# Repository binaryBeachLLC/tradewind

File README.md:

# Tradewind TW-1 · solar LoRaWAN field sensor

Tradewind is a sealed, solar-powered sensor for farms and remote sites. It measures air temperature and humidity,
soil moisture and rainfall, and reports over LoRaWAN every 5 minutes (every minute in rapid mode). It is a complete
reference design by [Binary Beach](https://binarybeach.tech): requirements, simulation, schematic, a 4-layer board,
enclosure, firmware, bring-up, characterization and a 30-day field pilot.

**The full story is in the documents. This README is a map of the repository.**

| | |
|---|---|
| 📘 [Engineering design & test report](docs/Tradewind_TW-1_Engineering_Report_revB.pdf) (46 pages) | requirements, simulation, schematic, electrical and layout considerations, EMI/EMC, enclosure, bring-up, test and field data |
| 📗 [Product datasheet](docs/Tradewind_TW-1_Datasheet_revB.pdf) (14 pages) | specifications, typical characteristics, connector functions, drawings, ordering |
| 🌐 [Interactive page](https://binarybeach.tech/hardware/tradewind/) | the product and the board in 3D, the schematic and the PCB layers in the browser |

## Results at a glance (rev B)

| | Measured | Requirement |
|---|---|---|
| Sleep current, whole device | 7.2 µA mean, 8.1 µA max (10 boards) | ≤ 10 µA |
| Average current, 5-min SF9 | 75.9 µA | ≤ 100 µA |
| Days with no sun at all, 1-min mode | ≈ 250 | ≥ 60 |
| Radio range, line of sight | decoded at 13.2 km (SF10) | ≥ 5 km |
| Air temperature error, −10 to +60 °C | 0.20 °C worst | ±0.3 °C |
| Hottest cell, 30 days in Hawaiʻi sun | 37.1 °C (air 31.9 °C) | < 45 °C |
| Uplinks received, 3 units × 30 days | 99.3 % | – |
| Electronics cost at 1,000 units | $16.43 (parts, PCB, assembly) | ≤ $25 |

13 of 15 requirements pass outright, R6 (charge window) passes marginally, and R10 (IP66 jet) is open pending an
accredited lab. See `test/compliance.csv`.

> Bench and field figures in this release are representative values for the reference design. The analysis scripts in
> `test/` run unchanged on new logs.

## How the design flows

```mermaid
flowchart LR
  spec[docs/design-spec.md] --> d[tools/design.py<br>parts · values · nets]
  d --> sch[gen_schematic.py<br>4-sheet KiCad schematic] --> erc[ERC + netlist check]
  d --> pcb[gen_pcb.py place<br>placement · planes · RF · fan-out] --> fr[Freerouting] --> ses[gen_pcb.py ses<br>import · pours · cleanup] --> drc[DRC + schematic parity]
  drc --> fab[export_fab.sh<br>Gerbers · BOM · CPL · STEP · GLB]
  spec --> sim[sim/<br>ngspice + Python]
  fab --> mech[mechanical/<br>CadQuery enclosure]
  fab --> rnd[render/<br>Blender Cycles]
  sim & mech & rnd & test[test/ analysis] --> docs[gen_report.py · gen_datasheet.py]
```

The schematic and the board are generated from one design file, `tools/design.py`, so they can't drift apart.
`tools/check_netlist.py` checks KiCad's exported netlist against that file pin by pin (233 pins, 47 nets), and DRC runs with schematic parity.
The KiCad project is an ordinary KiCad 9 project, so you can open it and edit it by hand.

## Repository walkthrough

```
docs/         design spec, report + datasheet (HTML sources and PDFs), figures, schematic PDF/SVG
hardware/     KiCad 9 project (tradewind/) and fabrication outputs (fab/)
mechanical/   CadQuery enclosure system: sources, STEP/STL/GLB, drawings, mechanical BOM
firmware/     RAK3172 / RUI3 firmware, payload codec, network-server decoder, host tests
sim/          10 simulations (ngspice decks + Python models) and their results
test/         test logs (CSV), analysis scripts, compliance table, bring-up log
render/       Blender render script and the renders
tools/        generators: schematic, PCB, 3D models, BOM, fab export, layout audit, docs, plot style
```

### `hardware/`: schematic and board
- `tradewind/tradewind.kicad_pro`: open this in KiCad 9. Root sheet plus `power`, `mcu_rf` and `sensors_io` sheets; `tradewind.kicad_pcb` is the routed board.
- `tradewind/tradewind.kicad_sym`: project symbol (DRV5032 hall switch). `tradewind/3d/` holds the 3D models we made because the library has none (RAK3172, JST PH side-entry, VQFN-16, SHT4x, 18650 cell).
- `fab/`: `tradewind_revB_gerbers.zip` (11 Gerber X2 layers plus drill), `assembly/tradewind_revB_cpl.csv`, `BOM_tradewind_revB.csv` (costed at 10/100/1k), `BOM_JLCPCB.csv`, the board as STEP and GLB, per-layer SVGs, `erc_report.txt` and `drc_report.txt`.
- Board: 96 × 70 mm, 4 layers (JLC 7628 stackup), matte black ENIG, 85 footprints, 50 Ω CPWG RF line, SHT40 on a slotted thermal island.
- `tools/layout_audit.py` measures the routed board (copper per net, current-path resistance, hot-loop areas, separations, RF geometry) into `fab/layout_audit.json`;
  `tools/layout_figs.py` draws the layout figures from it: each part outline comes from that part's pads, and numbered markers sit on computed features. The report's section 4 (electrical, BOM, layout, EMI/EMC) is built on those numbers.

### `sim/`: design analysis
Run `sim/run_all.sh` (about 20 s). It regenerates every `docs/figures/sim_*` figure and `sim/results.json`.

| Script | Question it answers |
|---|---|
| `solar_iv.py` | Does the charger's fixed 4.5 V input regulation get enough of the panel's power? (96–99 %) |
| `thermal_enclosure.py` | How hot does the cell get in the sun, and does the roof fix it? |
| `energy_year.py` | Is the device energy-positive for a whole Honolulu year, including an overcast week? |
| `power_budget.py` | Where does each uplink's charge go? What's the average current per mode? |
| `tx_droop.py` | Does +3V3 stay in spec during the 87 mA transmit burst? |
| `vbat_sense.py` | Why did rev A sleep at 34 µA? (battery divider leaking into the ADC clamp) |
| `rain_debounce.py` | Why did rev A double-count rain? (reed bounce) |
| `rf_match.py` | Antenna match in the closed case; 50 Ω trace geometry |
| `link_budget.py` | Range per spreading factor, and airtime |
| `board_si.py` | On the routed board: power-path drop, I²C over the probe cable, harmonic filtering, ADC settling |

### `mechanical/`: enclosure
`src/assembly.py` builds the whole system (box, lid, gasket, sun roof with panel, radiation shield, bracket, glands,
antenna) from parametric CadQuery parts. It checks fit against the board STEP and exports `out/tradewind_assembly.step`,
print-ready STLs and web GLBs. Materials, sealing math, print settings and the assembly order are in `mechanical/README.md`.

### `firmware/`: RAK3172 (STM32WLE5) on RUI3
Class A OTAA, US915 sub-band 2. Default interval 5 min, with a rapid 1-minute mode. Rain counting and magnet wake work while asleep.
`make test` runs the C++ payload tests and the JavaScript decoder tests against shared golden vectors.
The payload format is in `firmware/PAYLOAD.md`. The decoder for The Things Stack and ChirpStack is `firmware/decoder/ttn_decoder.js`.

### `test/`: characterization
`test/run_all.sh` turns the CSV logs in `test/data/` into every `docs/figures/test_*` figure, `results.json` and
`compliance.csv`. The test plan with pass criteria is `test/README.md`. The step-by-step bring-up (and the two rev A bugs) is in `test/BRINGUP.md`.

### `render/` and `docs/`
- `render/scripts/render.py`: Blender Cycles shots from the CAD and board exports (studio, outdoor, exploded, lid off, board, turntable).
- `tools/gen_report.py` and `tools/gen_datasheet.py` build `docs/report/` and `docs/datasheet/`. Every number comes from the result files, through `tools/docdata.py`.
- `tools/paginate.py` lays the report out in headless Chrome: each chapter flows across Letter pages, a heading never ends a page,
  and a full-width chart is never squeezed into half a column.
- `tools/build_docs.py --pdf` collects the images and prints both PDFs. `tools/check_pages.py` fails a page if its content overflows the Letter sheet.

## Rebuilding everything

| Tool | Used for |
|---|---|
| KiCad 9 (`snap install kicad`) | schematic, board, `kicad-cli` exports |
| Freerouting 1.9 + Java 21 | autorouting (run headless with `xvfb-run`) |
| conda env `environment.yml` | ngspice, CadQuery, numpy/scipy/matplotlib |
| Blender 4.2+ | renders |
| Google Chrome | PDF printing and page checks |

```bash
python3 tools/gen_schematic.py                                   # schematic from tools/design.py
snap run --shell kicad.kicad-cli -c "python3 tools/gen_pcb.py place && python3 tools/gen_pcb.py dsn"
(cd hardware/tradewind && xvfb-run -a java -jar freerouting-1.9.0.jar -de tradewind.dsn -do tradewind.ses -mp 40)
snap run --shell kicad.kicad-cli -c "python3 tools/gen_pcb.py ses"   # import routes, pour ground, clean up
tools/export_fab.sh                                              # ERC, DRC, Gerbers, BOM, CPL, STEP, GLB, renders, layout audit
sim/run_all.sh && test/run_all.sh                                # simulations and test analysis
python mechanical/src/assembly.py                                # enclosure (conda env)
blender -b --python render/scripts/render.py                     # renders
python3 tools/build_docs.py && (cd tools && python3 gen_report.py && python3 gen_datasheet.py) && python3 tools/build_docs.py --pdf
```

## License
Hardware (`hardware/`, `mechanical/`): [CERN-OHL-P-2.0](LICENSE-HARDWARE). Firmware, simulations and tools: [MIT](LICENSE).
Documentation, figures and renders: [CC BY 4.0](LICENSE-DOCS). Component datasheets belong to their manufacturers and are not included.

Designed by Maxwell Pauly · Binary Beach LLC · Honolulu, Hawaiʻi · maxwell.pauly@binarybeach.tech

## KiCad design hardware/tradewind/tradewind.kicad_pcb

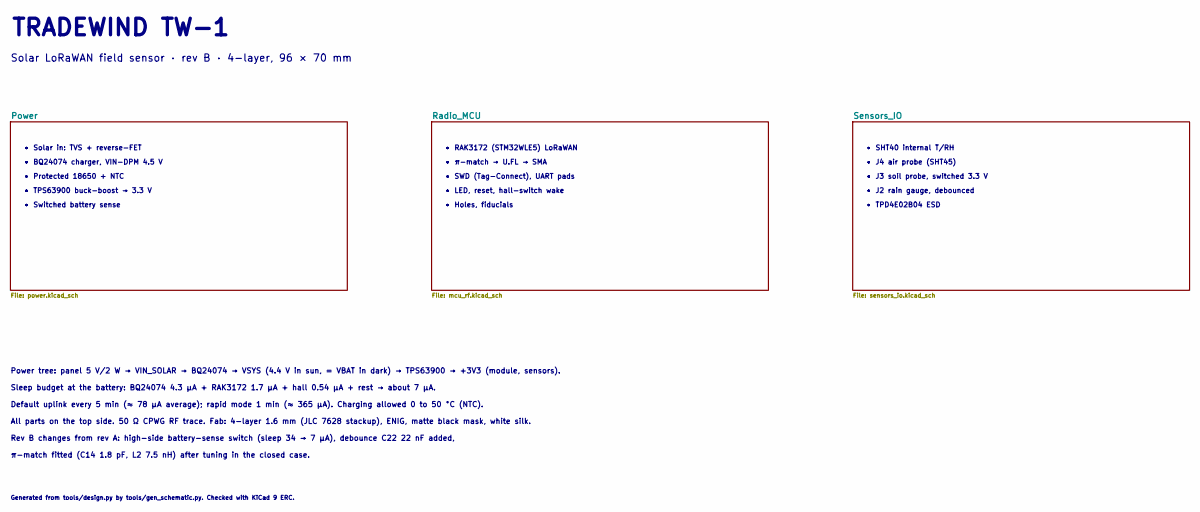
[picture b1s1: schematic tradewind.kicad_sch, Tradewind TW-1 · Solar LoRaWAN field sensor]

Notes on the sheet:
TRADEWIND TW-1
Solar LoRaWAN field sensor · rev B · 4-layer, 96 × 70 mm
• Solar in: TVS + reverse-FET
• BQ24074 charger, VIN-DPM 4.5 V
• Protected 18650 + NTC
• TPS63900 buck-boost → 3.3 V
• Switched battery sense
• RAK3172 (STM32WLE5) LoRaWAN
• π-match → U.FL → SMA
• SWD (Tag-Connect), UART pads
• LED, reset, hall-switch wake
• Holes, fiducials
• SHT40 internal T/RH
• J4 air probe (SHT45)
• J3 soil probe, switched 3.3 V
• J2 rain gauge, debounced
• TPD4E02B04 ESD
Power tree: panel 5 V/2 W → VIN_SOLAR → BQ24074 → VSYS (4.4 V in sun, = VBAT in dark) → TPS63900 → +3V3 (module, sensors).
Sleep budget at the battery: BQ24074 4.3 µA + RAK3172 1.7 µA + hall 0.54 µA + rest → about 7 µA.
Default uplink every 5 min (≈ 78 µA average); rapid mode 1 min (≈ 365 µA). Charging allowed 0 to 50 °C (NTC).
All parts on the top side. 50 Ω CPWG RF trace. Fab: 4-layer 1.6 mm (JLC 7628 stackup), ENIG, matte black mask, white silk.
Rev B changes from rev A: high-side battery-sense switch (sleep 34 → 7 µA), debounce C22 22 nF added,
π-match fitted (C14 1.8 pF, L2 7.5 nH) after tuning in the closed case.
Generated from tools/design.py by tools/gen_schematic.py. Checked with KiCad 9 ERC.

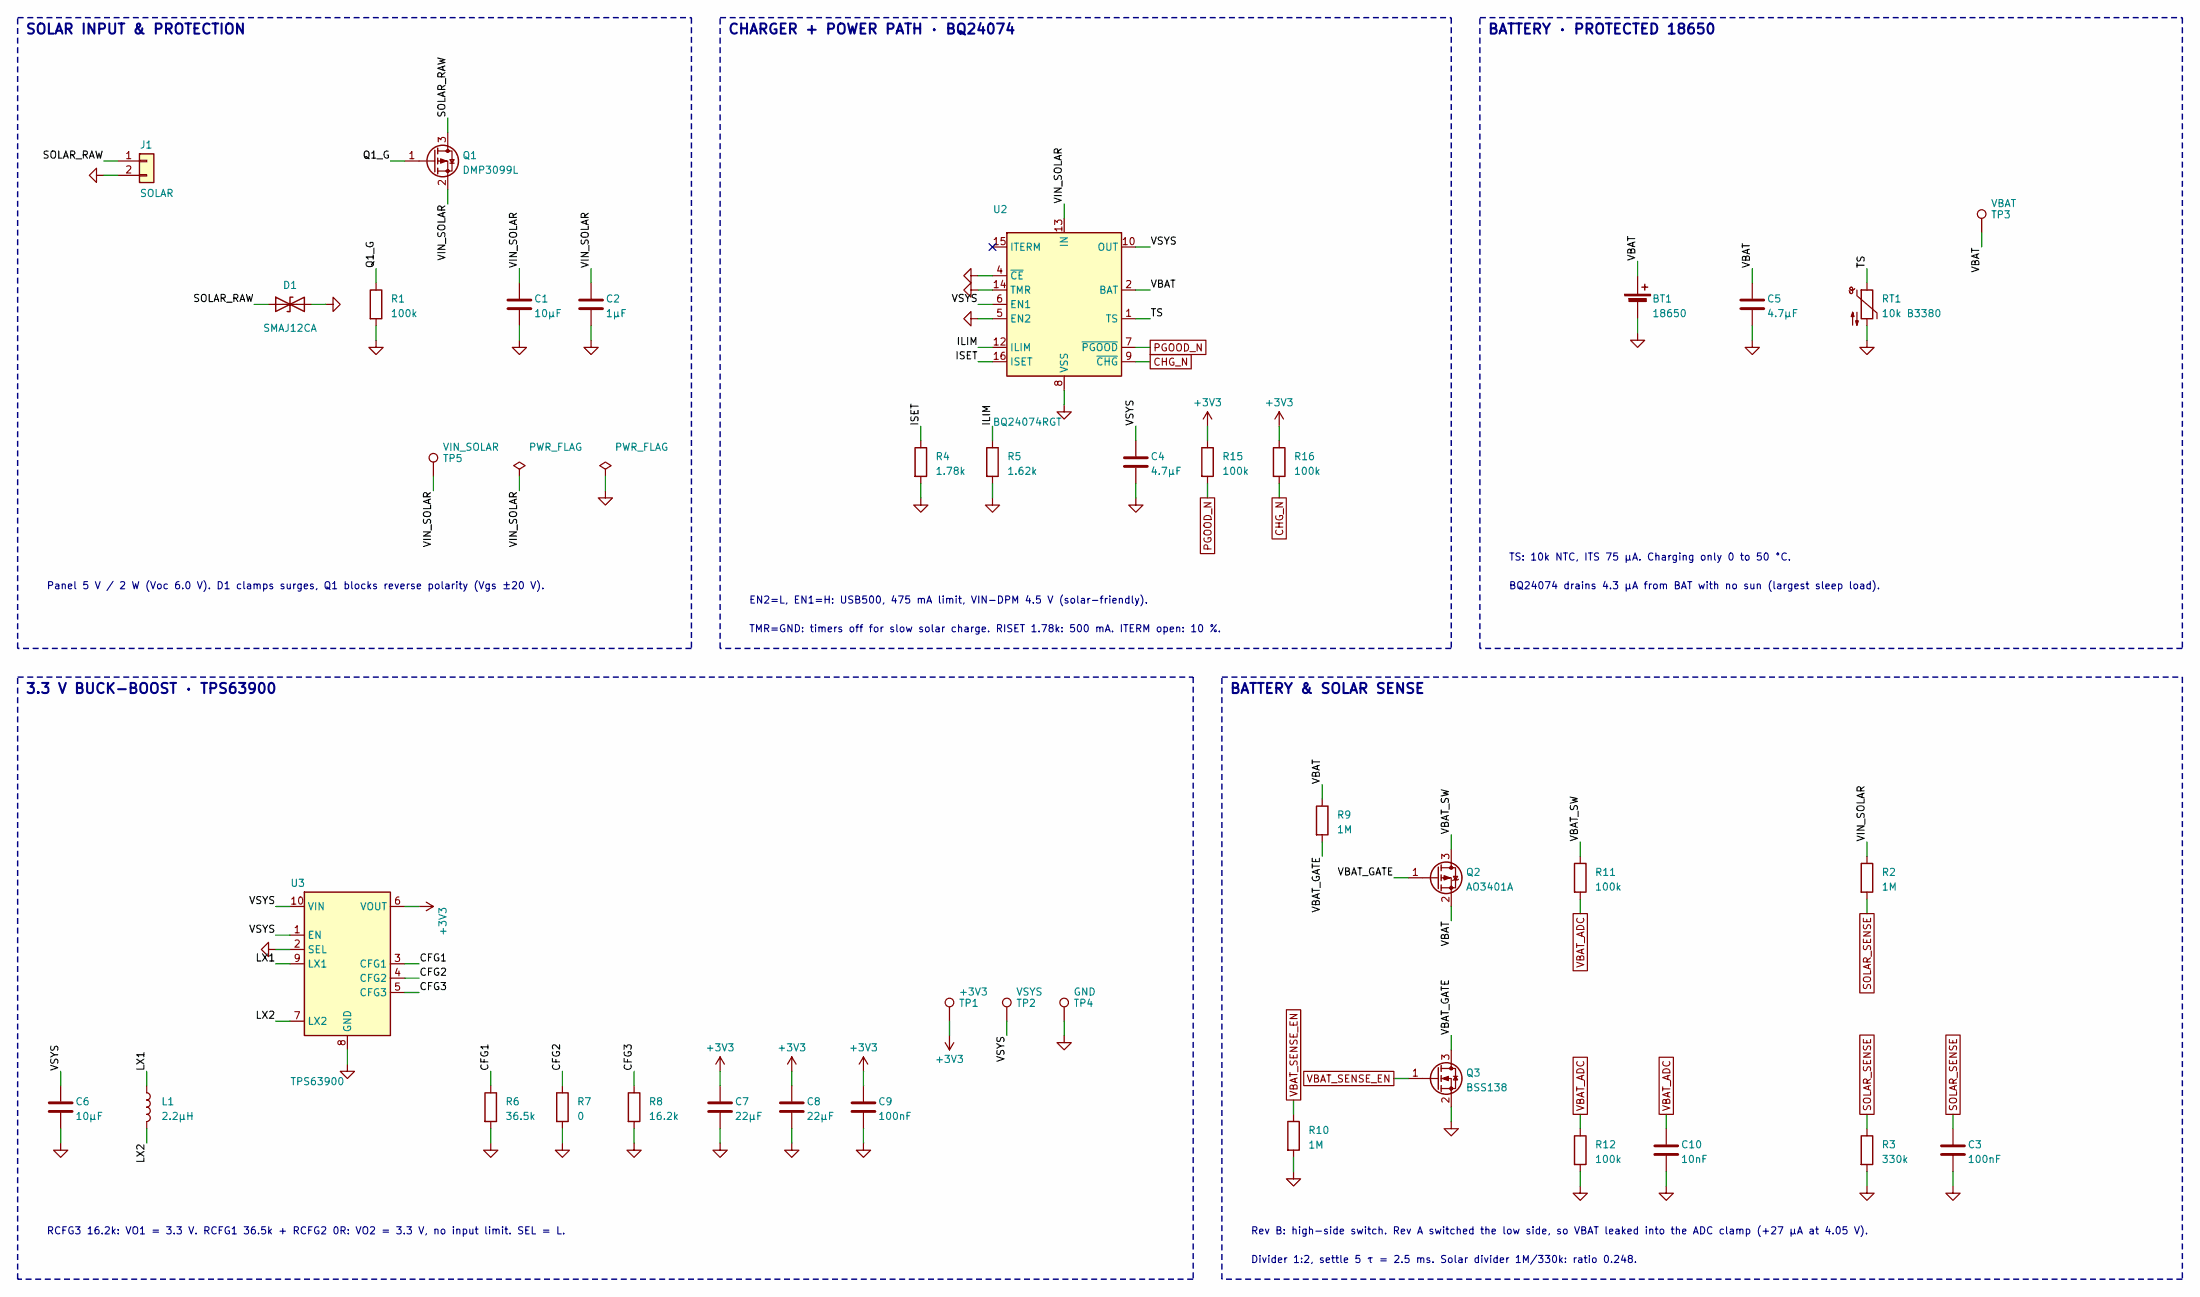
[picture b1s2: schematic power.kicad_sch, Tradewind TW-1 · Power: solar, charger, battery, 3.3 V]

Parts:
BT1: 18650; BatteryHolder_Keystone_1042_1x18650; MPN 1042
C1: 10µF; C_0805_2012Metric; MPN GRM21BR61E106KA73L
C2: 1µF; C_0603_1608Metric; MPN GRM188R61E105KA12D
C3, C9: 100nF; C_0402_1005Metric; MPN GRM155R71C104KA88D
C4, C5: 4.7µF; C_0603_1608Metric; MPN GRM188R61A475KE15D
C6: 10µF; C_0603_1608Metric; MPN GRM188R61A106KE69D
C7, C8: 22µF; C_0805_2012Metric; MPN GRM21BR61A226ME51L
C10: 10nF; C_0402_1005Metric; MPN GRM155R71C103KA01D
D1: SMAJ12CA; D_SMA; MPN SMAJ12CA
J1: SOLAR; JST_PH_S2B-PH-SM4-TB_1x02-1MP_P2.00mm_Horizontal; MPN S2B-PH-SM4-TB(LF)(SN)
L1: 2.2µH; L_1008_2520Metric; MPN DFE252012F-2R2M=P2
Q1: DMP3099L; SOT-23; MPN DMP3099L-7
Q2: AO3401A; SOT-23; MPN AO3401A
Q3: BSS138; SOT-23; MPN BSS138LT1G
R1, R11, R12, R15, R16: 100k; R_0402_1005Metric; MPN RC0402FR-07100KL
R2, R9, R10: 1M; R_0402_1005Metric; MPN RC0402FR-071ML
R3: 330k; R_0402_1005Metric; MPN RC0402FR-07330KL
R4: 1.78k; R_0402_1005Metric; MPN RC0402FR-071K78L
R5: 1.62k; R_0402_1005Metric; MPN RC0402FR-071K62L
R6: 36.5k; R_0402_1005Metric; MPN RC0402FR-0736K5L
R7: 0; R_0402_1005Metric; MPN RC0402JR-070RL
R8: 16.2k; R_0402_1005Metric; MPN RC0402FR-0716K2L
RT1: 10k B3380; R_0402_1005Metric; MPN NCP15XH103F03RC
TP1: +3V3; TestPoint_Pad_D1.0mm
TP2: VSYS; TestPoint_Pad_D1.0mm
TP3: VBAT; TestPoint_Pad_D1.0mm
TP4: GND; TestPoint_Pad_D1.0mm
TP5: VIN_SOLAR; TestPoint_Pad_D1.0mm
U2: BQ24074RGT; VQFN-16-1EP_3x3mm_P0.5mm_EP1.6x1.6mm; MPN BQ24074RGTR
U3: TPS63900; WSON-10-1EP_2.5x2.5mm_P0.5mm_EP1.2x2mm_ThermalVias; MPN TPS63900DSKR

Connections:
+3V3: C7.1, C8.1, C9.1, R15.1, R16.1, TP1.1, U3.6 (VOUT); also elsewhere on the board
/Power/CFG1: R6.1, U3.3 (CFG1)
/Power/CFG2: R7.1, U3.4 (CFG2)
/Power/CFG3: R8.1, U3.5 (CFG3)
/Power/ILIM: R5.1, U2.12 (ILIM)
/Power/ISET: R4.1, U2.16 (ISET)
/Power/LX1: L1.1, U3.9 (LX1)
/Power/LX2: L1.2, U3.7 (LX2)
/Power/Q1_G: Q1.1 (G), R1.1
/Power/SOLAR_RAW: D1.1 (A1), J1.1, Q1.3 (D)
/Power/TS: RT1.1, U2.1 (TS)
/Power/VBAT: BT1.1 (+), C5.1, Q2.2 (S), R9.1, TP3.1, U2.2 (BAT), U2.3 (BAT)
/Power/VBAT_GATE: Q2.1 (G), Q3.3 (D), R9.2
/Power/VBAT_SW: Q2.3 (D), R11.1
/Power/VIN_SOLAR: C1.1, C2.1, Q1.2 (S), R2.1, TP5.1, U2.13 (IN)
/Power/VSYS: C4.1, C6.1, TP2.1, U2.6 (EN1), U2.10 (OUT), U2.11 (OUT), U3.1 (EN), U3.10 (VIN)
CHG_N: R16.2, U2.9 (~CHG); also elsewhere on the board
GND: BT1.2 (-), C1.2, C2.2, C3.2, C4.2, C5.2, C6.2, C7.2, C8.2, C9.2, C10.2, D1.2 (A2), J1.2, Q3.2 (S), R1.2, R3.2, R4.2, R5.2, R6.2, R7.2, R8.2, R10.2, R12.2, RT1.2, TP4.1, U2.4 (~CE), U2.5 (EN2), U2.8 (VSS), U2.14 (TMR), U2.17 (VSS), U3.2 (SEL), U3.8 (GND), U3.11 (GND); also elsewhere on the board
PGOOD_N: R15.2, U2.7 (~PGOOD); also elsewhere on the board
SOLAR_SENSE: C3.1, R2.2, R3.1; also elsewhere on the board
VBAT_ADC: C10.1, R11.2, R12.1; also elsewhere on the board
VBAT_SENSE_EN: Q3.1 (G), R10.1; also elsewhere on the board

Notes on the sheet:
SOLAR INPUT & PROTECTION
CHARGER + POWER PATH · BQ24074
BATTERY · PROTECTED 18650
3.3 V BUCK-BOOST · TPS63900
BATTERY & SOLAR SENSE
Panel 5 V / 2 W (Voc 6.0 V). D1 clamps surges, Q1 blocks reverse polarity (Vgs ±20 V).
EN2=L, EN1=H: USB500, 475 mA limit, VIN-DPM 4.5 V (solar-friendly).
TMR=GND: timers off for slow solar charge. RISET 1.78k: 500 mA. ITERM open: 10 %.
TS: 10k NTC, ITS 75 µA. Charging only 0 to 50 °C.
BQ24074 drains 4.3 µA from BAT with no sun (largest sleep load).
RCFG3 16.2k: VO1 = 3.3 V. RCFG1 36.5k + RCFG2 0R: VO2 = 3.3 V, no input limit. SEL = L.
Rev B: high-side switch. Rev A switched the low side, so VBAT leaked into the ADC clamp (+27 µA at 4.05 V).
Divider 1:2, settle 5 τ = 2.5 ms. Solar divider 1M/330k: ratio 0.248.

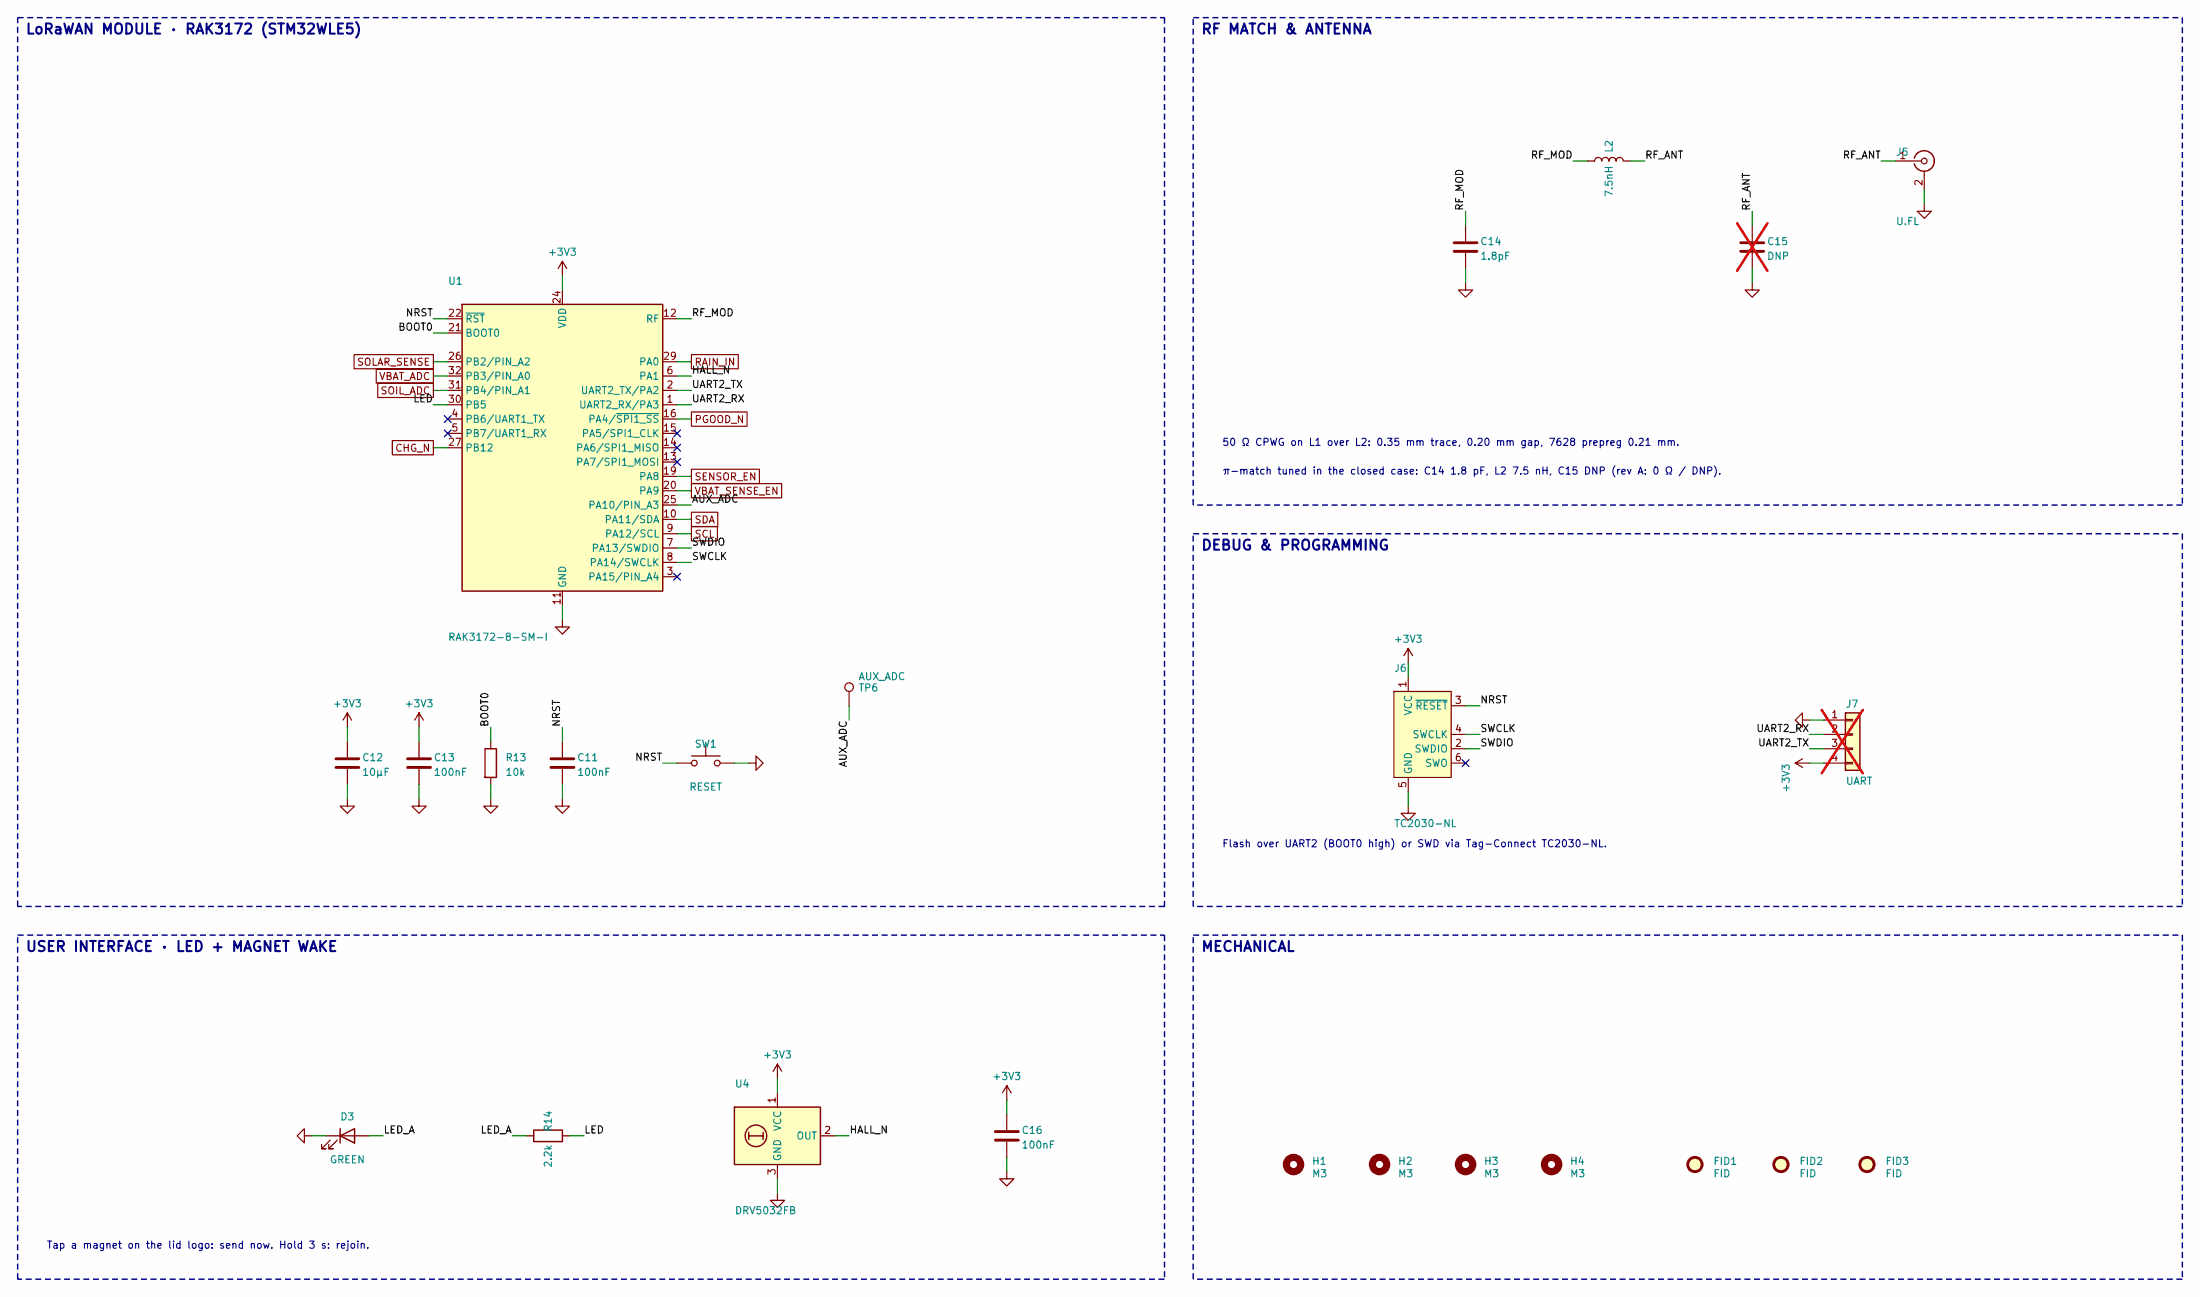
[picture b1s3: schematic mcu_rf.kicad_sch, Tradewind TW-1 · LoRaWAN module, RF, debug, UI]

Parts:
C11, C13, C16: 100nF; C_0402_1005Metric; MPN GRM155R71C104KA88D
C12: 10µF; C_0603_1608Metric; MPN GRM188R61A106KE69D
C14: 1.8pF; C_0402_1005Metric; MPN GJM1555C1H1R8BB01D
C15: DNP; C_0402_1005Metric; not fitted
D3: GREEN; LED_0603_1608Metric; MPN LTST-C191KGKT
FID1, FID2, FID3: FID; Fiducial_1mm_Mask2mm
H1, H2, H3, H4: M3; MountingHole_3.2mm_M3
J5: U.FL; U.FL_Hirose_U.FL-R-SMT-1_Vertical; MPN U.FL-R-SMT-1(10)
J6: TC2030-NL; Tag-Connect_TC2030-IDC-NL_2x03_P1.27mm_Vertical
J7: UART; PinHeader_1x04_P1.27mm_Vertical; not fitted
L2: 7.5nH; L_0402_1005Metric; MPN LQG15HS7N5J02D
R13: 10k; R_0402_1005Metric; MPN RC0402FR-0710KL
R14: 2.2k; R_0402_1005Metric; MPN RC0402FR-072K2L
SW1: RESET; SW_SPST_B3U-1000P; MPN B3U-1000P
TP6: AUX_ADC; TestPoint_Pad_D1.0mm
U1: RAK3172-8-SM-I; RAK3172; MPN RAK3172-8-SM-I
U4: DRV5032FB; SOT-23; MPN DRV5032FBDBZR

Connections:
+3V3: C12.1, C13.1, C16.1, J6.1 (VCC), J7.4, U1.24 (VDD), U4.1 (VCC); also elsewhere on the board
/Radio_MCU/AUX_ADC: TP6.1, U1.25 (PA10/PIN_A3)
/Radio_MCU/BOOT0: R13.1, U1.21 (BOOT0)
/Radio_MCU/HALL_N: U1.6 (PA1), U4.2 (OUT)
/Radio_MCU/LED: R14.2, U1.30 (PB5)
/Radio_MCU/LED_A: D3.2 (A), R14.1
/Radio_MCU/NRST: C11.1, J6.3 (~RESET), SW1.1, U1.22 (~RST)
/Radio_MCU/RF_ANT: C15.1, J5.1 (In), L2.2
/Radio_MCU/RF_MOD: C14.1, L2.1, U1.12 (RF)
/Radio_MCU/SWCLK: J6.4 (SWCLK), U1.8 (PA14/SWCLK)
/Radio_MCU/SWDIO: J6.2 (SWDIO), U1.7 (PA13/SWDIO)
/Radio_MCU/UART2_RX: J7.2, U1.1 (UART2_RX/PA3)
/Radio_MCU/UART2_TX: J7.3, U1.2 (UART2_TX/PA2)
CHG_N: U1.27 (PB12); also elsewhere on the board
GND: C11.2, C12.2, C13.2, C14.2, C15.2, C16.2, D3.1 (K), J5.2 (Ext), J6.5 (GND), J7.1, R13.2, SW1.2, U1.11 (GND), U1.17 (GND), U1.18 (GND), U1.23 (GND), U1.28 (GND), U4.3 (GND); also elsewhere on the board
PGOOD_N: U1.16 (PA4/~SPI1_SS); also elsewhere on the board
RAIN_IN: U1.29 (PA0); also elsewhere on the board
SCL: U1.9 (PA12/SCL); also elsewhere on the board
SDA: U1.10 (PA11/SDA); also elsewhere on the board
SENSOR_EN: U1.19 (PA8); also elsewhere on the board
SOIL_ADC: U1.31 (PB4/PIN_A1); also elsewhere on the board
SOLAR_SENSE: U1.26 (PB2/PIN_A2); also elsewhere on the board
VBAT_ADC: U1.32 (PB3/PIN_A0); also elsewhere on the board
VBAT_SENSE_EN: U1.20 (PA9); also elsewhere on the board

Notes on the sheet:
LoRaWAN MODULE · RAK3172 (STM32WLE5)
RF MATCH & ANTENNA
DEBUG & PROGRAMMING
USER INTERFACE · LED + MAGNET WAKE
MECHANICAL
50 Ω CPWG on L1 over L2: 0.35 mm trace, 0.20 mm gap, 7628 prepreg 0.21 mm.
π-match tuned in the closed case: C14 1.8 pF, L2 7.5 nH, C15 DNP (rev A: 0 Ω / DNP).
Flash over UART2 (BOOT0 high) or SWD via Tag-Connect TC2030-NL.
Tap a magnet on the lid logo: send now. Hold 3 s: rejoin.

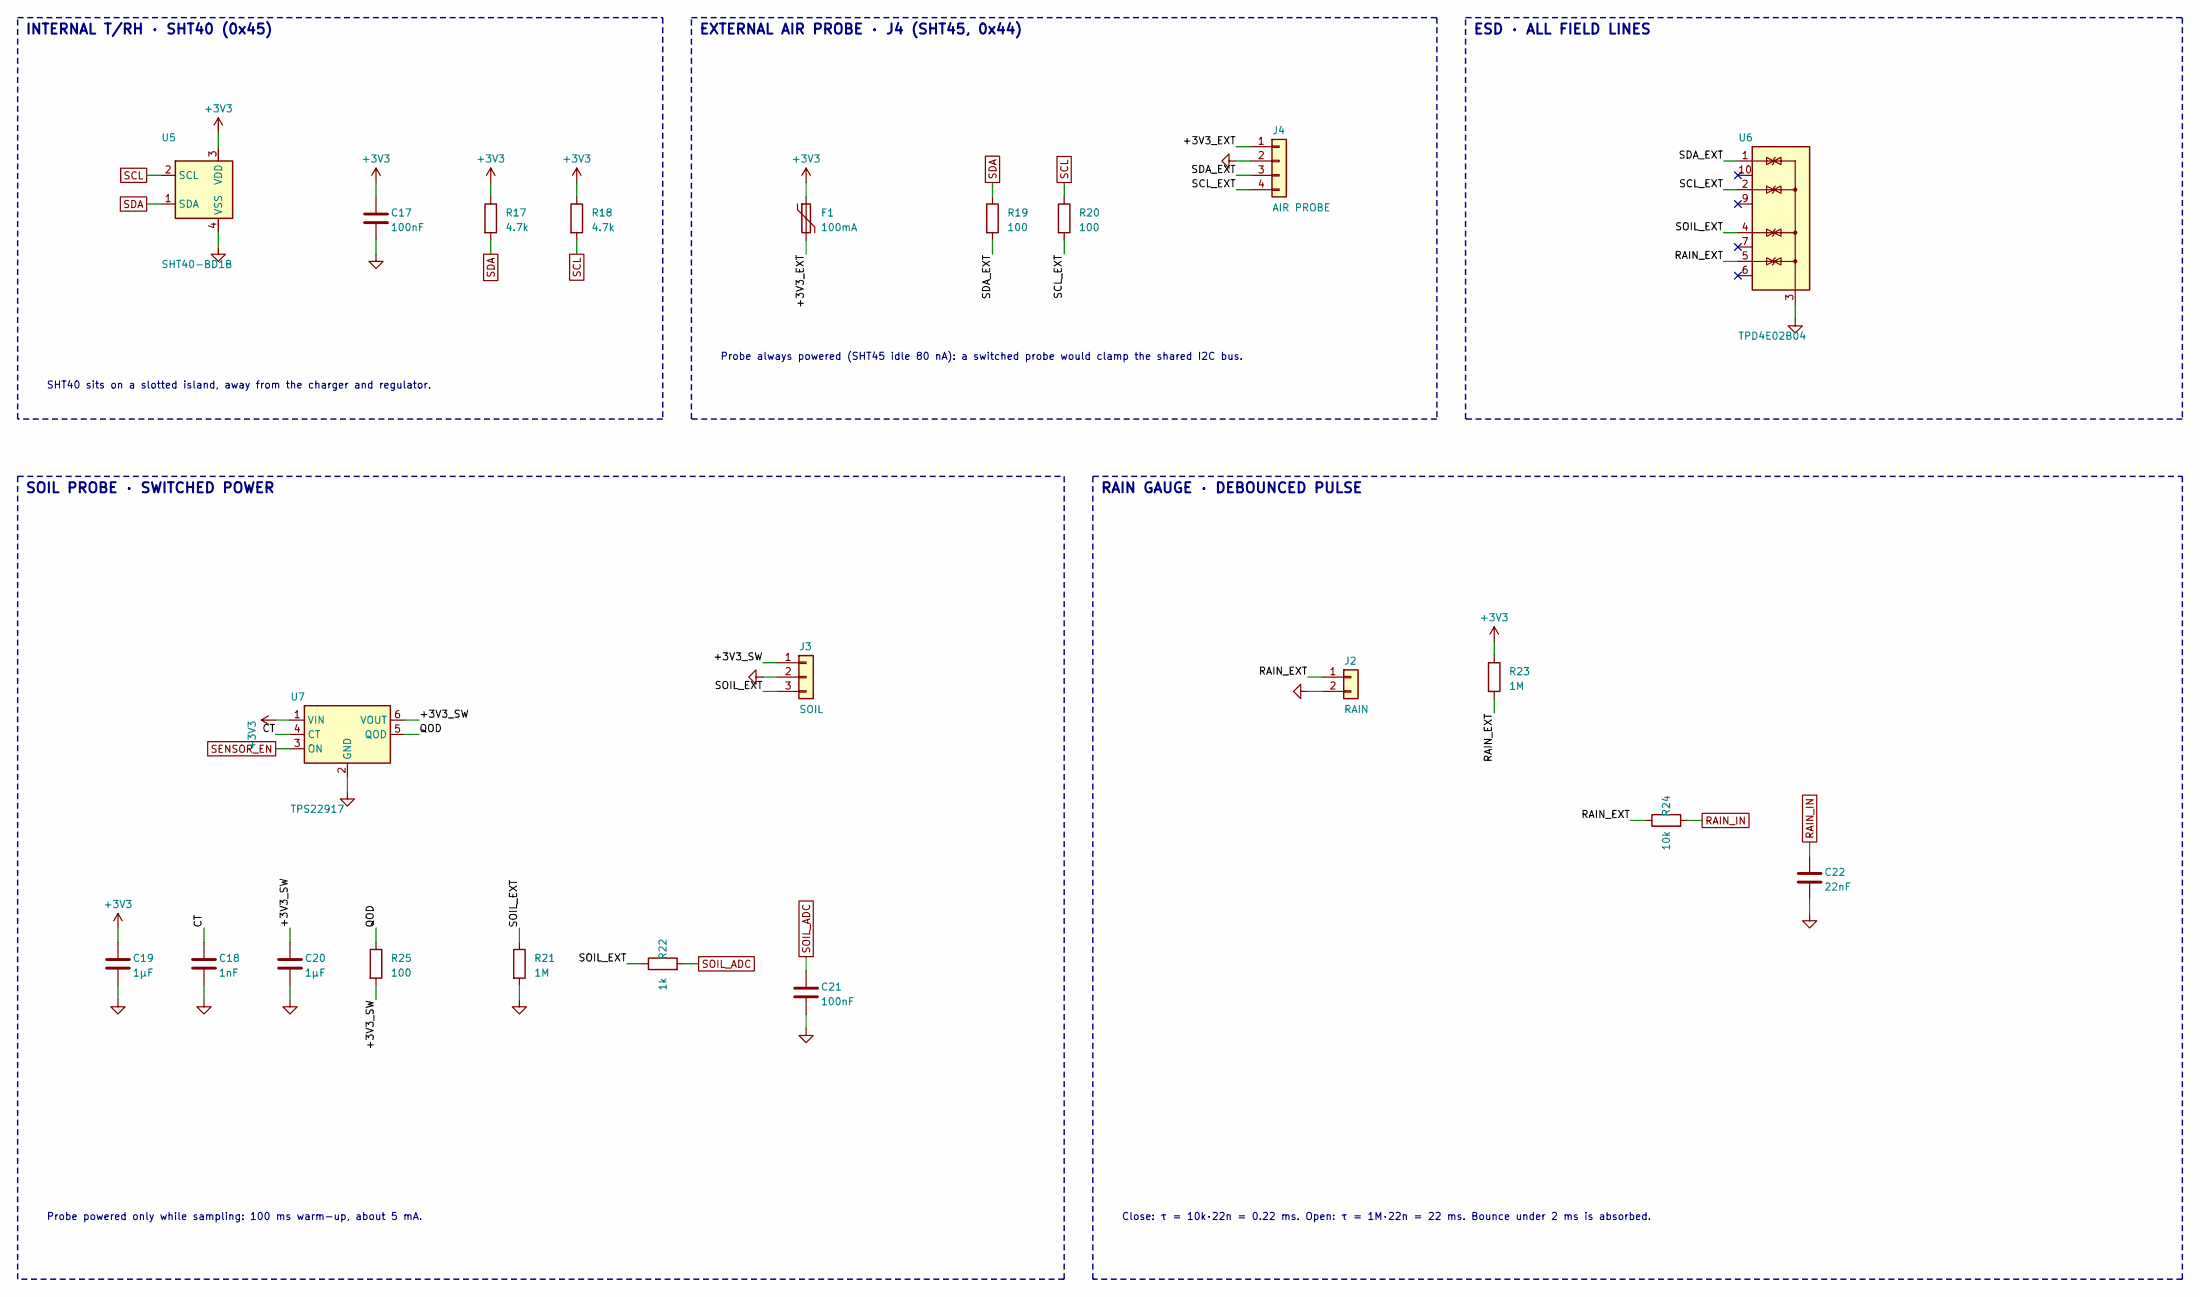
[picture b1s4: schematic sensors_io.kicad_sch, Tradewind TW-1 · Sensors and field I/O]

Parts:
C17, C21: 100nF; C_0402_1005Metric; MPN GRM155R71C104KA88D
C18: 1nF; C_0402_1005Metric; MPN GRM155R71H102KA01D
C19, C20: 1µF; C_0402_1005Metric; MPN GRM155R61A105KE15D
C22: 22nF; C_0402_1005Metric; MPN GRM155R71C223KA01D
F1: 100mA; Fuse_0805_2012Metric; MPN MF-PSMF010X-2
J2: RAIN; JST_PH_S2B-PH-SM4-TB_1x02-1MP_P2.00mm_Horizontal; MPN S2B-PH-SM4-TB(LF)(SN)
J3: SOIL; JST_PH_S3B-PH-SM4-TB_1x03-1MP_P2.00mm_Horizontal; MPN S3B-PH-SM4-TB(LF)(SN)
J4: AIR PROBE; JST_PH_S4B-PH-SM4-TB_1x04-1MP_P2.00mm_Horizontal; MPN S4B-PH-SM4-TB(LF)(SN)
R17, R18: 4.7k; R_0402_1005Metric; MPN RC0402FR-074K7L
R19, R20, R25: 100; R_0402_1005Metric; MPN RC0402FR-07100RL
R21, R23: 1M; R_0402_1005Metric; MPN RC0402FR-071ML
R22: 1k; R_0402_1005Metric; MPN RC0402FR-071KL
R24: 10k; R_0402_1005Metric; MPN RC0402FR-0710KL
U5: SHT40-BD1B; Sensirion_DFN-4_1.5x1.5mm_P0.8mm_SHT4x_NoCentralPad; MPN SHT40-BD1B-R2
U6: TPD4E02B04; USON-10_2.5x1.0mm_P0.5mm; MPN TPD4E02B04DQAR
U7: TPS22917; SOT-23-6; MPN TPS22917DBVR

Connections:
+3V3: C17.1, C19.1, F1.1, R17.1, R18.1, R23.1, U5.3 (VDD), U7.1 (VIN); also elsewhere on the board
/Sensors_IO/+3V3_EXT: F1.2, J4.1
/Sensors_IO/+3V3_SW: C20.1, J3.1, R25.2, U7.6 (VOUT)
/Sensors_IO/CT: C18.1, U7.4 (CT)
/Sensors_IO/QOD: R25.1, U7.5 (QOD)
/Sensors_IO/RAIN_EXT: J2.1, R23.2, R24.1, U6.5 (IO4)
/Sensors_IO/SCL_EXT: J4.4, R20.2, U6.2 (IO2)
/Sensors_IO/SDA_EXT: J4.3, R19.2, U6.1 (IO1)
/Sensors_IO/SOIL_EXT: J3.3, R21.1, R22.1, U6.4 (IO3)
GND: C17.2, C18.2, C19.2, C20.2, C21.2, C22.2, J2.2, J3.2, J4.2, R21.2, U5.4 (VSS), U6.3 (G), U6.8 (G), U7.2 (GND); also elsewhere on the board
RAIN_IN: C22.1, R24.2; also elsewhere on the board
SCL: R18.2, R20.1, U5.2 (SCL); also elsewhere on the board
SDA: R17.2, R19.1, U5.1 (SDA); also elsewhere on the board
SENSOR_EN: U7.3 (ON); also elsewhere on the board
SOIL_ADC: C21.1, R22.2; also elsewhere on the board

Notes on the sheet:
INTERNAL T/RH · SHT40 (0x45)
EXTERNAL AIR PROBE · J4 (SHT45, 0x44)
ESD · ALL FIELD LINES
SOIL PROBE · SWITCHED POWER
RAIN GAUGE · DEBOUNCED PULSE
Probe always powered (SHT45 idle 80 nA): a switched probe would clamp the shared I2C bus.
SHT40 sits on a slotted island, away from the charger and regulator.
Probe powered only while sampling: 100 ms warm-up, about 5 mA.
Close: τ = 10k·22n = 0.22 ms. Open: τ = 1M·22n = 22 ms. Bounce under 2 ms is absorbed.

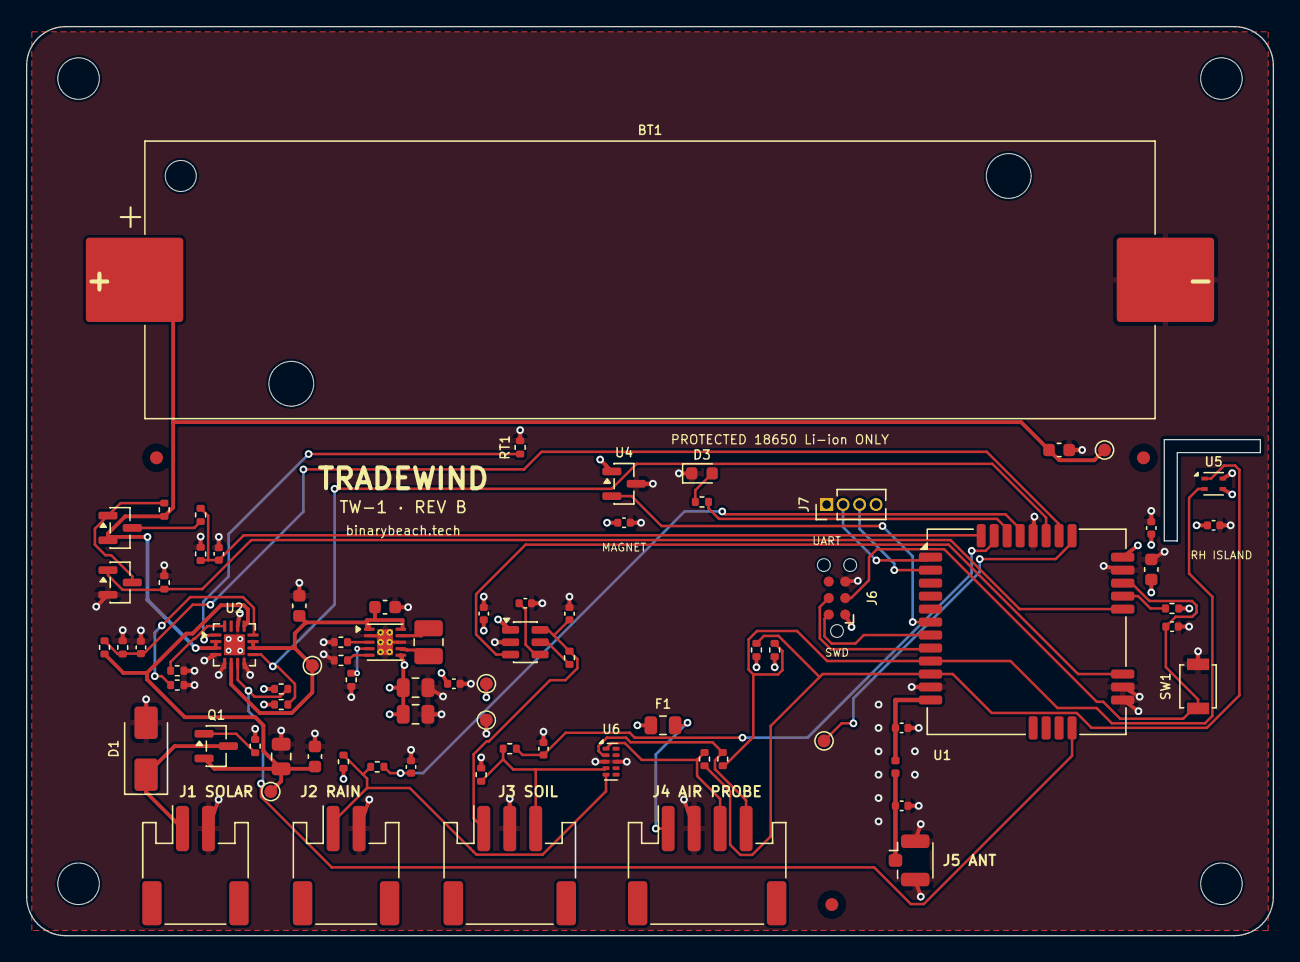
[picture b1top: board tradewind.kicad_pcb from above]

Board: 4 copper layers, 96.0 x 70.0 mm, 85 parts (0 on the bottom side), 47 nets.

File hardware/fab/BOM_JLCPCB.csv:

Comment,Designator,Footprint,LCSC Part #
SOLAR S2B-PH-SM4-TB(LF)(SN),J1,JST_PH_S2B-PH-SM4-TB_1x02-1MP_P2.00mm_Horizontal,
SMAJ12CA SMAJ12CA,D1,D_SMA,C113951
DMP3099L DMP3099L-7,Q1,SOT-23,C155407
100k RC0402FR-07100KL,"R1,R11,R12,R15,R16",R_0402_1005Metric,
10µF GRM21BR61E106KA73L,C1,C_0805_2012Metric,
1µF GRM188R61E105KA12D,C2,C_0603_1608Metric,
BQ24074RGT BQ24074RGTR,U2,VQFN-16-1EP_3x3mm_P0.5mm_EP1.6x1.6mm,C54313
1.78k RC0402FR-071K78L,R4,R_0402_1005Metric,
1.62k RC0402FR-071K62L,R5,R_0402_1005Metric,
4.7µF GRM188R61A475KE15D,"C4,C5",C_0603_1608Metric,
18650 1042,BT1,BatteryHolder_Keystone_1042_1x18650,
10k B3380 NCP15XH103F03RC,RT1,R_0402_1005Metric,
TPS63900 TPS63900DSKR,U3,WSON-10-1EP_2.5x2.5mm_P0.5mm_EP1.2x2mm_ThermalVias,C2683460
10µF GRM188R61A106KE69D,"C6,C12",C_0603_1608Metric,
2.2µH DFE252012F-2R2M=P2,L1,L_1008_2520Metric,
36.5k RC0402FR-0736K5L,R6,R_0402_1005Metric,
0 RC0402JR-070RL,R7,R_0402_1005Metric,
16.2k RC0402FR-0716K2L,R8,R_0402_1005Metric,
22µF GRM21BR61A226ME51L,"C7,C8",C_0805_2012Metric,
100nF GRM155R71C104KA88D,"C3,C9,C11,C13,C16,C17,C21",C_0402_1005Metric,
AO3401A AO3401A,Q2,SOT-23,C15127
1M RC0402FR-071ML,"R2,R9,R10,R21,R23",R_0402_1005Metric,
BSS138 BSS138LT1G,Q3,SOT-23,C78284
10nF GRM155R71C103KA01D,C10,C_0402_1005Metric,
330k RC0402FR-07330KL,R3,R_0402_1005Metric,
RAK3172-8-SM-I RAK3172-8-SM-I,U1,RAK3172,C2924540
10k RC0402FR-0710KL,"R13,R24",R_0402_1005Metric,
RESET B3U-1000P,SW1,SW_SPST_B3U-1000P,
U.FL U.FL-R-SMT-1(10),J5,U.FL_Hirose_U.FL-R-SMT-1_Vertical,C88374
7.5nH LQG15HS7N5J02D,L2,L_0402_1005Metric,
1.8pF GJM1555C1H1R8BB01D,C14,C_0402_1005Metric,
GREEN LTST-C191KGKT,D3,LED_0603_1608Metric,
2.2k RC0402FR-072K2L,R14,R_0402_1005Metric,
DRV5032FB DRV5032FBDBZR,U4,SOT-23,C1850416
SHT40-BD1B SHT40-BD1B-R2,U5,Sensirion_DFN-4_1.5x1.5mm_P0.8mm_SHT4x_NoCentralPad,C2758077
4.7k RC0402FR-074K7L,"R17,R18",R_0402_1005Metric,
AIR PROBE S4B-PH-SM4-TB(LF)(SN),J4,JST_PH_S4B-PH-SM4-TB_1x04-1MP_P2.00mm_Horizontal,
100mA MF-PSMF010X-2,F1,Fuse_0805_2012Metric,
100 RC0402FR-07100RL,"R19,R20,R25",R_0402_1005Metric,
TPD4E02B04 TPD4E02B04DQAR,U6,USON-10_2.5x1.0mm_P0.5mm,C1974361
TPS22917 TPS22917DBVR,U7,SOT-23-6,C2155396
1µF GRM155R61A105KE15D,"C19,C20",C_0402_1005Metric,
1nF GRM155R71H102KA01D,C18,C_0402_1005Metric,
SOIL S3B-PH-SM4-TB(LF)(SN),J3,JST_PH_S3B-PH-SM4-TB_1x03-1MP_P2.00mm_Horizontal,
1k RC0402FR-071KL,R22,R_0402_1005Metric,
RAIN S2B-PH-SM4-TB(LF)(SN),J2,JST_PH_S2B-PH-SM4-TB_1x02-1MP_P2.00mm_Horizontal,
22nF GRM155R71C223KA01D,C22,C_0402_1005Metric,

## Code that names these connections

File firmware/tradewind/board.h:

// Tradewind TW-1 rev B — RAK3172 pin map. Matches docs/design-spec.md §4 and the schematic.
#pragma once

// Analog inputs
#define PIN_VBAT_ADC       PB3   // A0: VBAT / 2 through the high-side switched divider (R11/R12, C10)
#define PIN_SOIL_ADC       PB4   // A1: soil probe output (R22 1 k / C21 100 nF)
#define PIN_SOLAR_SENSE    PB2   // A2: VIN_SOLAR x 0.2481 (R2 1 M / R3 330 k, C3 100 nF)
#define PIN_AUX_ADC        PA10  // A3: test pad TP6, unused in firmware

// Digital
#define PIN_RAIN_IN        PA0   // tipping-bucket reed, active low, RC-debounced (R23/R24/C22)
#define PIN_HALL_N         PA1   // DRV5032FB push-pull, low while a magnet is near the lid logo
#define PIN_SENSOR_EN      PA8   // TPS22917 ON -> +3V3_SW (soil probe power)
#define PIN_VBAT_SENSE_EN  PA9   // BSS138 gate -> AO3401A high-side switch on the VBAT divider
#define PIN_LED            PB5   // green LED via 2.2 k (~0.5 mA)
#define PIN_CHG_N          PB12  // BQ24074 ~CHG, open drain, 100 k pull-up
#define PIN_PGOOD_N        PA4   // BQ24074 ~PGOOD, open drain, 100 k pull-up
// I2C (Wire): PA11 SDA, PA12 SCL, 4.7 k pull-ups. Internal SHT40 0x45, external SHT45 probe 0x44.
// SWD on PA13/PA14 (Tag-Connect J6). UART2 PA2/PA3 is the RUI3 AT/flash port (J7).

// Analog scaling
#define ADC_BITS           12
#define ADC_FULL_SCALE_MV  3300.0f     // analogReference(RAK_ADC_MODE_DEFAULT): VDD = 3.3 V; confirm at bring-up
#define VBAT_DIVIDER       2.0f        // 100 k / 100 k
#define SOLAR_DIVIDER      (1.0f / 0.2481f)

// Timings. VBAT divider: tau = 0.5 ms, 12-bit settling (½ LSB) needs 4.5 ms (sim/board_si.py; was 3 ms in the
// pilot firmware, 0.25 % low). Probe warm-up per vendor.
#define VBAT_SETTLE_MS     5
#define SOIL_WARMUP_MS     100

// I2C addresses
#define SHT_EXT_ADDR       0x44        // SHT45-AD1B in the radiation shield
#define SHT_INT_ADDR       0x45        // SHT40-BD1B on the board island

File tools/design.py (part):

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
# ---------------------------------------------------------------- power sheet
S = "power"
P("J1", "Connector_Generic:Conn_01x02", "SOLAR", FP["PH2"], S, 16, 20, {"1": "SOLAR_RAW", "2": "GND"},
  mpn="S2B-PH-SM4-TB(LF)(SN)", mfr="JST", desc="Solar panel input, JST PH 2-pin side entry")
P("D1", "Device:D_TVS", "SMAJ12CA", FP["SMA"], S, 26, 30, {"1": "SOLAR_RAW", "2": "GND"},
  mpn="SMAJ12CA", mfr="Littelfuse", desc="TVS, 12 V standoff, 400 W, bidirectional")
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
P("J5", "Connector:Conn_Coaxial", "U.FL", FP["UFL"], S, 140, 20, {"1": "RF_ANT", "2": "GND"},
  mpn="U.FL-R-SMT-1(10)", mfr="Hirose", desc="U.FL receptacle to SMA bulkhead pigtail")
P("L2", "Device:L", "7.5nH", FP["L0402"], S, 118, 20, {"1": "RF_MOD", "2": "RF_ANT"}, rot=90,
  mpn="LQG15HS7N5J02D", mfr="Murata", desc="7.5 nH ±5 % 0402 (π-match series; rev A: 0 Ω)")
Cap("C14", "1.8pF", S, 108, 26, "RF_MOD", "GND", "GJM1555C1H1R8BB01D", desc="1.8 pF ±0.1 pF C0G 0402 (π-match shunt, module side)")
Cap("C15", "DNP", S, 128, 26, "RF_ANT", "GND", "", desc="π-match shunt, connector side (not fitted)", dnp=True)
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Cap("C18", "1nF", S, 20, 76, "CT", "GND", "GRM155R71H102KA01D", desc="1 nF 50 V X7R 0402 (slew control)")
R("R25", "100", S, 32, 76, "QOD", "+3V3_SW", "RC0402FR-07100RL")
Cap("C20", "1µF", S, 26, 76, "+3V3_SW", "GND", "GRM155R61A105KE15D", desc="1 µF 10 V X5R 0402")
P("J3", "Connector_Generic:Conn_01x03", "SOIL", FP["PH3"], S, 62, 56, {"1": "+3V3_SW", "2": "GND", "3": "SOIL_EXT"},
  mpn="S3B-PH-SM4-TB(LF)(SN)", mfr="JST", desc="Capacitive soil-moisture probe")
R("R21", "1M", S, 42, 76, "SOIL_EXT", "GND", "RC0402FR-071ML")
R("R22", "1k", S, 52, 76, "SOIL_EXT", "SOIL_ADC", "RC0402FR-071KL", rot=90)
Cap("C21", "100nF", S, 62, 78, "SOIL_ADC", "GND", "GRM155R71C104KA88D", desc="100 nF 16 V X7R 0402")

P("J2", "Connector_Generic:Conn_01x02", "RAIN", FP["PH2"], S, 100, 56, {"1": "RAIN_EXT", "2": "GND"},
  mpn="S2B-PH-SM4-TB(LF)(SN)", mfr="JST", desc="Tipping-bucket rain gauge (reed)")
R("R23", "1M", S, 110, 56, "+3V3", "RAIN_EXT", "RC0402FR-071ML")
R("R24", "10k", S, 122, 66, "RAIN_EXT", "RAIN_IN", "RC0402FR-0710KL", rot=90)
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
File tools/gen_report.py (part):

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at the input limit; a Schottky would drop about 0.35 V, which the 4.5 V input-regulation point can't spare.
C1 10 µF / 25 V keeps about half its value at 5 V of bias, inside the charger's 1–10 µF range for IN.</td></tr>
<tr><td><b>Charger</b><br>U2 BQ24074</td><td>USB500 mode (EN1 = VSYS, EN2 = GND): the input is limited to 475 mA and <b>VIN-DPM</b> holds the panel at 4.5 V,
which is the reason this part works without an MPPT chip. EN1 is tied to VSYS, not to the panel, because the EN pins are rated 7 V.
ISET 1.78 kΩ sets 500 mA. TMR is grounded so the safety timers can't end a slow solar charge. The TS NTC limits charging to about 0–50 °C.
ILIM is fitted as the datasheet asks (USB500 ignores it). CHG and PGOOD pull up to +3V3, not VSYS, so the MCU pins never exceed VDD.</td></tr>
</table>
""")
page(f"""
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<p class="small">1 oz outer copper; ΔT from the IPC-2221 external-layer curve. A 0.3 mm track carries {f(LA['paths'][0]['ampacity_10C_A'],1)} A for a 10 °C rise,
so heating is never the issue; <b>resistance is</b>. The drops that matter: the {f(pth['Charger BAT → cell +']['drop_mV'],0)} mV on VBAT during constant-current charge
makes the charger enter constant-voltage about {f(pth['Charger BAT → cell +']['drop_mV'],0)} mV early, which lengthens the charge slightly but costs no capacity
(the drop falls to ~3 mV at the 50 mA termination current). VIN_SOLAR's {f(pth['Reverse FET → charger IN']['drop_mV'],0)} mV is harmless: VIN-DPM regulates at the IN pin, so the panel simply runs
{f(pth['Reverse FET → charger IN']['drop_mV'],0)} mV higher on its curve. Rev C widens VBAT to 1 mm ({f(si['vbat_revC_1mm']['drop_mV'],0)} mV).</p>
<h3>Plane pair and decoupling</h3>
<p class="small">L2 (GND) and L3 (+3V3) are 1.07 mm apart, which gives only {f(si['plane_pair_pF'],0)} pF of plane capacitance. The design doesn't rely on it.
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<h3>Sensitive nets</h3>
<table class="small"><tr><th>Net</th><th>Why it's sensitive</th><th>Treatment</th></tr>
<tr><td>CFG1–3</td><td>Read once; a misread sets VOUT</td><td>≤ 1.9 mm, 1 % / 100 ppm</td></tr>
<tr><td>ISET, ILIM</td><td>Set the charge current</td><td>Resistors at the pins</td></tr>
<tr><td>TS</td><td>NTC voltage sets the charge window</td><td>Kept {f(sep_['Switch node → battery ADC net'],0)}+ mm from the switch node</td></tr>
<tr><td>VBAT_ADC</td><td>50 kΩ source</td><td>10 nF at the divider; trace driven from 10 nF</td></tr>
<tr><td>SOLAR_SENSE</td><td>248 kΩ source</td><td>100 nF at the divider</td></tr>
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<p class="small">Rev A: 3 boards, hand-assembled (stencil, hot plate, rework station). Rev B: 10 boards assembled by the board house.
The full step-by-step log is in <code>test/BRINGUP.md</code>.</p>
<table class="small"><tr><th>Rev A issue</th><th>How we found it</th><th>Root cause</th><th>Rev B fix (verified)</th></tr>
<tr><td>Sleep 34 µA (budget 7)</td><td>PPK2, part-lifting; current scaled with VBAT</td><td>Low-side divider switch: PB3 sat at VBAT and leaked through the clamp diode</td><td>High-side P-FET switch (Q2/Q3). {f(bu['sleep_uA_3V7']['mean'],1)} µA mean on 10 boards</td></tr>
<tr><td>2–6 rain counts per tip</td><td>50 hand tips counted 173</td><td>Reed bounce on an unfiltered EXTI input</td><td>10 kΩ / 22 nF filter + 50 ms firmware lockout. {env['rain_bench']['tips_counted']}/{env['rain_bench']['tips_applied']} on the bench</td></tr>
<tr><td>S11 −11 dB at 915 in the case</td><td>NanoVNA through the U.FL with the lid closed</td><td>Plastic and pigtail detune the whip</td><td>π-match C14 1.8 pF / L2 7.5 nH: {f(rft['s11']['case_matched_revB']['at_915_dB'],1)} dB</td></tr>
</table>
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

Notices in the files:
hardware/tradewind/tradewind.kicad_pcb:
Binary Beach LLC · Honolulu, Hawaiʻi · CERN-OHL-P-2.0
